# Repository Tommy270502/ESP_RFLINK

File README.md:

# Wireless Dev Bridge

Wireless Dev Bridge is a USB-C developer kit for ESP32-S3 and nRF24L01+ work. It gives one bench dongle a shared JSON command protocol over USB serial, HTTP, WebSocket, and BLE, plus a Python SDK, CLI, local web workbench, firmware browser dashboard, KiCad hardware source, and manufacturing outputs.

## Start Here

1. Read [Getting Started](docs/getting-started.md) for firmware build, SDK install, and first RF validation.
2. Use the local web workbench:

   ```bash
   pip install -r application/requirements.txt
   python application/main.py
   ```

3. Or install the SDK and CLI:

   ```bash
   cd sdk/python
   python -m pip install -e ".[all]"
   wdb discover
   wdb --serial COM5 identify
   wdb --serial COM5 diagnostics
   ```

4. For a two-dongle kit, flash one `node1` and one `node2`, then run:

   ```bash
   wdb pair-test --node1-serial COM5 --node2-serial COM6
   ```

## Product Surfaces

| Surface | Location | Description |
| --- | --- | --- |
| Firmware | `Firmware/ESP32_RFLINK` | PlatformIO ESP32-S3 firmware. |
| Local web workbench | `application` | FastAPI/browser host tool at `http://127.0.0.1:5173`. |
| SDK/CLI | `sdk/python` | Python SDK, CLI, examples, and hardware-free tests. |
| Firmware browser dashboard | `http://192.168.4.1` | Served by the dongle SoftAP. |
| Hardware | `hardware/kicad` | KiCad schematic and PCB source. |
| Manufacturing | `manufacturing/gerbers` | Current V1 Gerber/drill export. |

All transports share one command response envelope:

```json
{"ok":true,"cmd":"status","data":{},"error":null}
```

See [Project Overview](project-overview.md) for interfaces, validated bench workflows, and architecture detail.

## Protocol 1.1 Capabilities

- Shared command envelope over USB serial, HTTP, WebSocket, and BLE.
- Runtime RF config, address management, send/listen/flush, and bridge toggles.
- Settings persistence through NVS with `settings_get`, `settings_set`, `settings_save`, and `settings_reset`.
- Diagnostics and identify commands for support and physical device matching.
- Optional token auth for HTTP, WebSocket, and BLE command surfaces.
- Support report export from the CLI and local web workbench.

## Development Checks

```bash
cd Firmware/ESP32_RFLINK
pio run -e node1 -e node2

cd ../../sdk/python
python -m pytest

cd ../..
python -m py_compile application/main.py
python scripts/check_docs_links.py
```

## Documentation

- [Documentation Index](docs/documentation-index.md)
- [Project Overview](project-overview.md)
- [Getting Started](docs/getting-started.md)
- [First Run](docs/first-run.md)
- [API Reference](docs/api-reference.md)
- [Firmware Guide](docs/firmware.md)
- [Hardware Guide](docs/hardware.md)
- [Security Model](docs/security-model.md)
- [Troubleshooting](docs/troubleshooting.md)
- [Release Checklist](docs/release-checklist.md)
- [Local Web Workbench](application/desktop-workbench.md)
- [Python SDK](sdk/python/python-sdk-guide.md)

## V1 Boundaries

- nRF24 payloads are limited to 32 bytes.
- nRF24 address width is fixed at 5 bytes.
- RF configuration is runtime-only until saved with protocol 1.1 settings commands.
- HTTP, WebSocket, and BLE APIs are intended for trusted developer/lab networks.
- OTA, cloud connectivity, packet decoding, persistence, and mesh networking are out of scope for V1.

## License

Software is licensed under the MIT License; see [LICENSE](LICENSE). Hardware source and manufacturing outputs use the hardware license notice in [hardware/LICENSE.md](hardware/LICENSE.md).

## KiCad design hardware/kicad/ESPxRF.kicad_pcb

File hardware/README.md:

# Hardware

KiCad hardware source and project-local mechanical assets for Wireless Dev Bridge V1.

Open the KiCad project at:

```text
hardware/kicad/ESPxRF.kicad_pro
```

Manufacturing outputs are kept separately in:

```text
manufacturing/gerbers
```

See [Hardware Guide](../docs/hardware.md) for board assets, KiCad notes, manufacturing review steps, and firmware pin alignment.

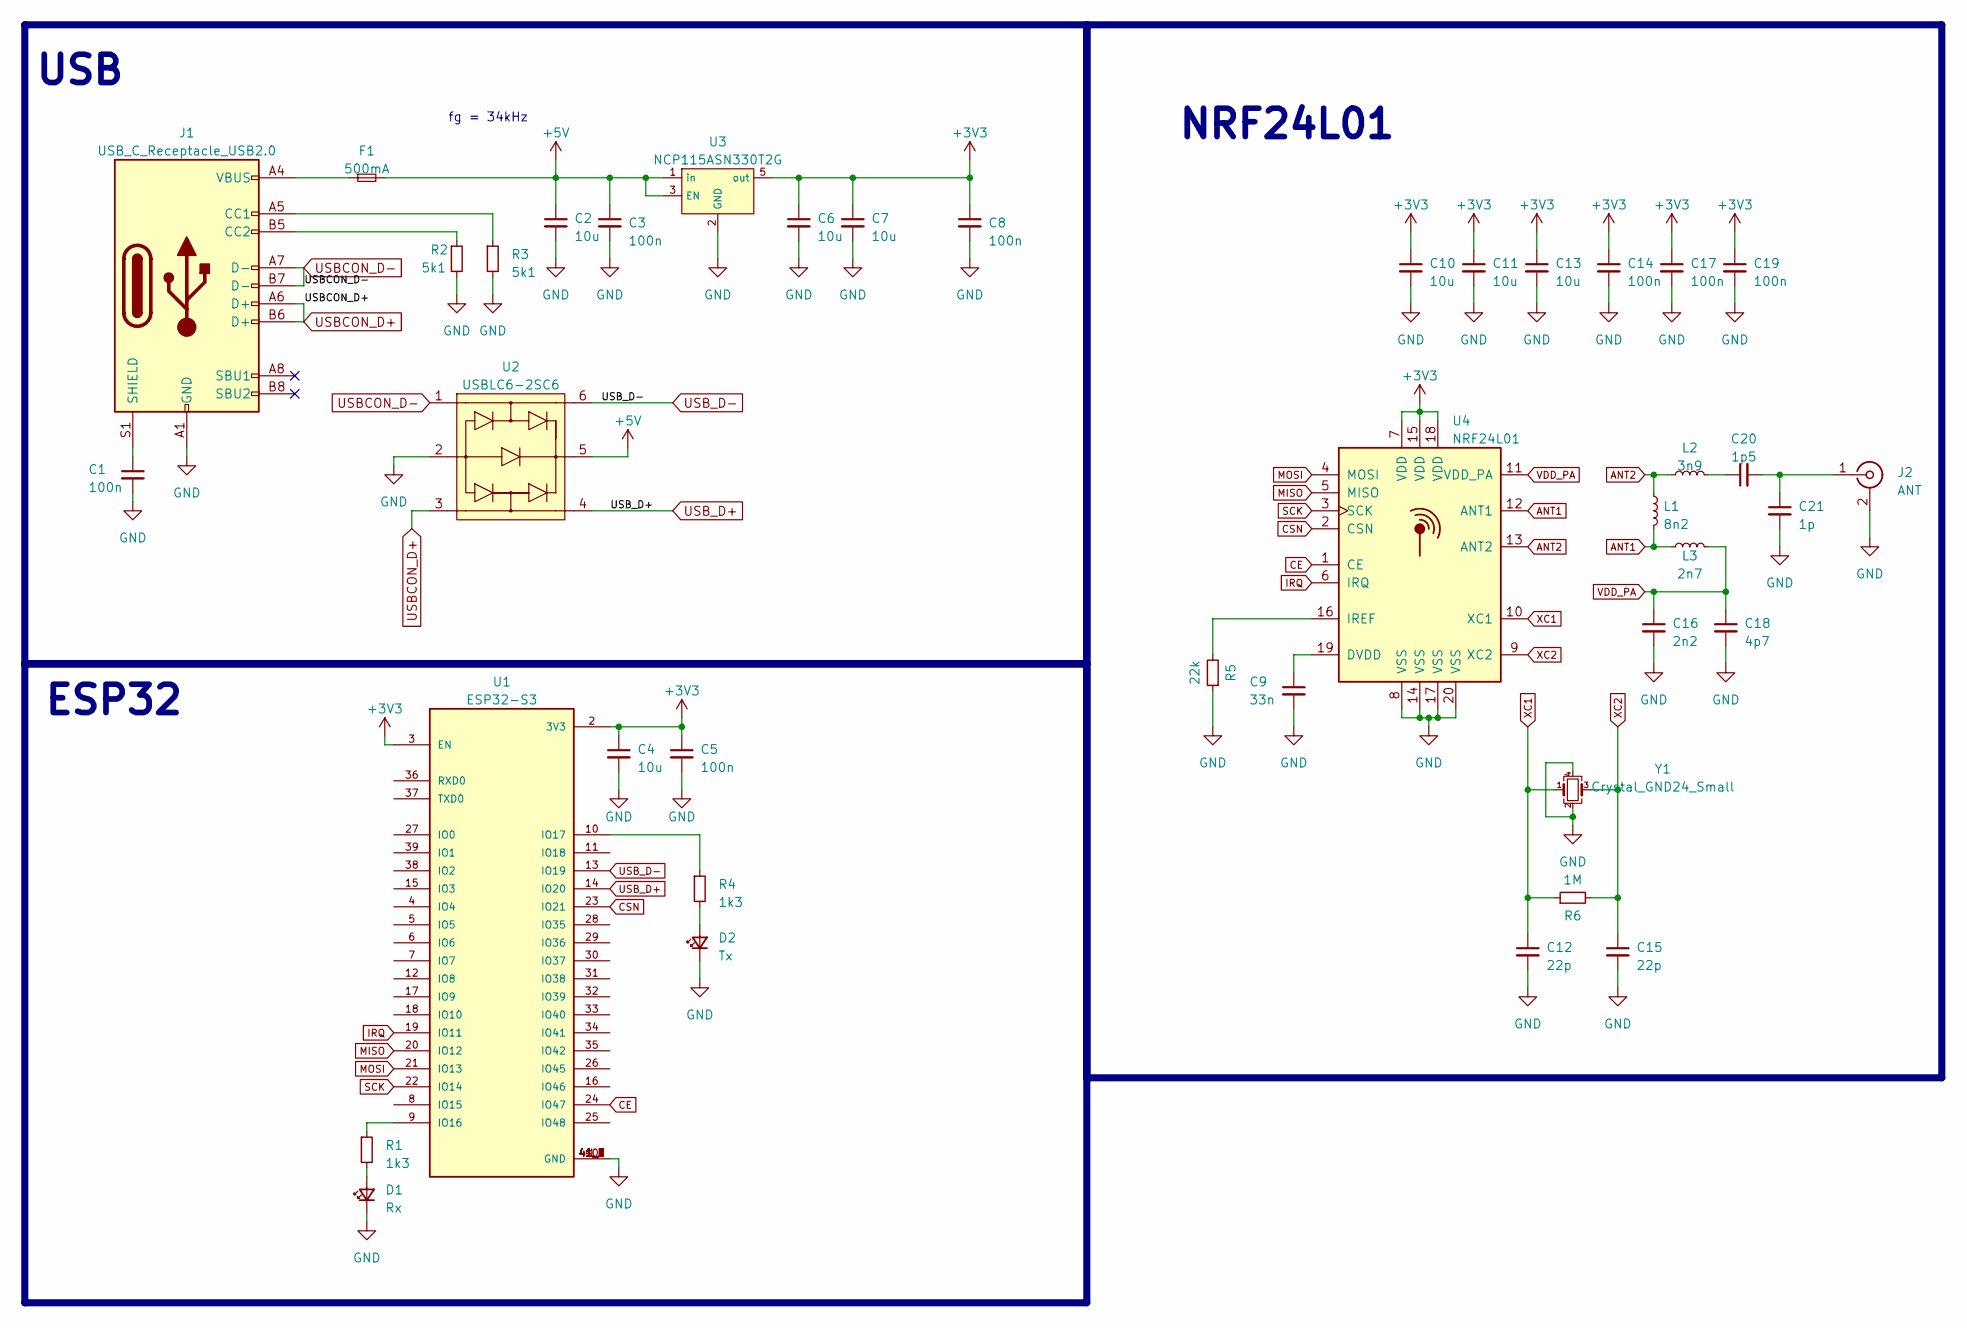
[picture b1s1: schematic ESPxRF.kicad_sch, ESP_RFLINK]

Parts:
C1, C3, C5, C8, C14, C17, C19: 100n; C_0603_1608Metric_Pad1.08x0.95mm_HandSolder
C2, C4, C6, C7, C10, C11, C13: 10u; C_0805_2012Metric_Pad1.18x1.45mm_HandSolder
C9: 33n; C_0603_1608Metric_Pad1.08x0.95mm_HandSolder
C12, C15: 22p; C_0603_1608Metric_Pad1.08x0.95mm_HandSolder
C16: 2n2; C_0402_1005Metric_Pad0.74x0.62mm_HandSolder
C18: 4p7; C_0402_1005Metric_Pad0.74x0.62mm_HandSolder
C20: 1p5; C_0402_1005Metric_Pad0.74x0.62mm_HandSolder
C21: 1p; C_0402_1005Metric_Pad0.74x0.62mm_HandSolder
D1: Rx; LED_0603_1608Metric_Pad1.05x0.95mm_HandSolder
D2: Tx; LED_0603_1608Metric_Pad1.05x0.95mm_HandSolder
F1: 500mA; Fuse_0603_1608Metric_Pad1.05x0.95mm_HandSolder
J1: USB_C_Receptacle_USB2.0; USB_C_Receptacle_GCT_USB4105-xx-A_16P_TopMnt_Horizontal
J2: ANT; SMA_Samtec_SMA-J-P-H-ST-EM1_EdgeMount
L1: 8n2; L_0402_1005Metric_Pad0.77x0.64mm_HandSolder
L2: 3n9; L_0402_1005Metric_Pad0.77x0.64mm_HandSolder
L3: 2n7; L_0402_1005Metric_Pad0.77x0.64mm_HandSolder
R1, R4: 1k3; R_0603_1608Metric_Pad0.98x0.95mm_HandSolder
R2, R3: 5k1; R_0603_1608Metric_Pad0.98x0.95mm_HandSolder
R5: 22k; R_0603_1608Metric_Pad0.98x0.95mm_HandSolder
R6: 1M; R_0603_1608Metric_Pad0.98x0.95mm_HandSolder
U1: ESP32-S3; XCVR_ESP32S3WROOM1N8R8
U2: USBLC6-2SC6; SOT-23-6_Handsoldering
U3: NCP115ASN330T2G; SOT-23-5_HandSoldering
U4: NRF24L01; QFN-20-1EP_4x4mm_P0.5mm_EP2.5x2.5mm
Y1: Crystal_GND24_Small; Crystal_SMD_2520-4Pin_2.5x2.0mm

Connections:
+3V3: C4.1, C5.1, C6.1, C7.1, C8.1, C10.1, C11.1, C13.1, C14.1, C17.1, C19.1, U1.2 (3V3), U1.3 (EN), U3.5 (out), U4.7 (VDD), U4.15 (VDD), U4.18 (VDD)
+5V: C2.1, C3.1, F1.2, U2.5, U3.1 (in), U3.3 (EN)
ANT1: L1.2, L3.1, U4.12 (ANT1)
ANT2: L1.1, L2.1, U4.13 (ANT2)
CE: U1.24 (IO47), U4.1 (CE)
CSN: U1.23 (IO21), U4.2 (CSN)
GND: C1.2, C2.2, C3.2, C4.2, C5.2, C6.2, C7.2, C8.2, C9.2, C10.2, C11.2, C12.2, C13.2, C14.2, C15.2, C16.2, C17.2, C18.2, C19.2, C21.2, D1.1 (K), D2.1 (K), J1.A1 (GND), J1.A12 (GND), J1.B1 (GND), J1.B12 (GND), J2.2 (Ext), R2.2, R3.2, R5.1, U1.1 (GND), U1.40 (GND), U1.41_1 (GND), U1.41_2 (GND), U1.41_3 (GND), U1.41_4 (GND), U1.41_5 (GND), U1.41_6 (GND), U1.41_7 (GND), U1.41_8 (GND), U1.41_9 (GND), U2.2, U3.2 (GND), U4.8 (VSS), U4.14 (VSS), U4.17 (VSS), U4.20 (VSS), Y1.2, Y1.4
IRQ: U1.19 (IO11), U4.6 (IRQ)
MISO: U1.20 (IO12), U4.5 (MISO)
MOSI: U1.21 (IO13), U4.4 (MOSI)
unnamed: C20.1, L2.2
unnamed: D1.2 (A), R1.2
unnamed: D2.2 (A), R4.2
unnamed: F1.1, J1.A4 (VBUS), J1.A9 (VBUS), J1.B4 (VBUS), J1.B9 (VBUS)
unnamed: J1.A5 (CC1), R3.1
unnamed: J1.B5 (CC2), R2.1
unnamed: C1.1, J1.S1 (SHIELD)
unnamed: C20.2, C21.1, J2.1 (In)
unnamed: R1.1, U1.9 (IO16)
unnamed: R4.1, U1.10 (IO17)
unnamed: C9.1, U4.19 (DVDD)
unnamed: R5.2, U4.16 (IREF)
SCK: U1.22 (IO14), U4.3 (SCK)
USBCON_D+: J1.A6 (D+), J1.B6 (D+), U2.3
USBCON_D-: J1.A7 (D-), J1.B7 (D-), U2.1
USB_D+: U1.14 (IO20), U2.4
USB_D-: U1.13 (IO19), U2.6
VDD_PA: C16.1, C18.1, L3.2, U4.11 (VDD_PA)
XC1: C12.1, R6.1, U4.10 (XC1), Y1.1
XC2: C15.1, R6.2, U4.9 (XC2), Y1.3

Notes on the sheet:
ESP32
fg = 34kHz
USB
NRF24L01

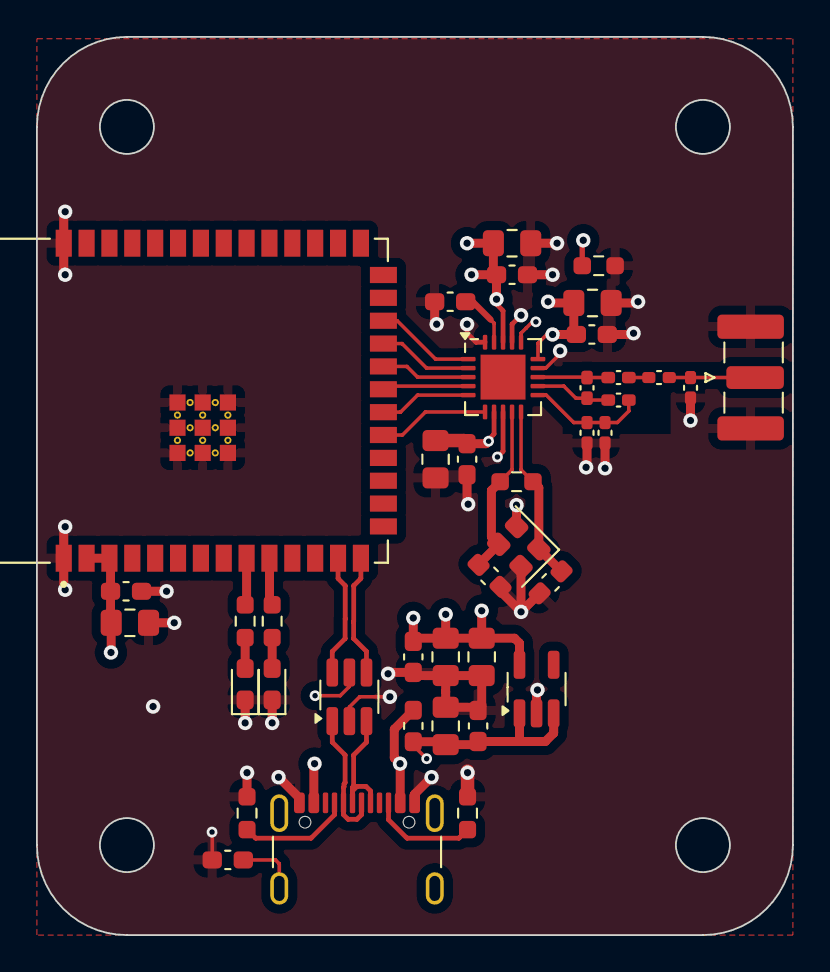
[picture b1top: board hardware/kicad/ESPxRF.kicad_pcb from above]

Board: 4 copper layers, 42.0 x 49.9 mm, 40 parts (0 on the bottom side), 30 nets.

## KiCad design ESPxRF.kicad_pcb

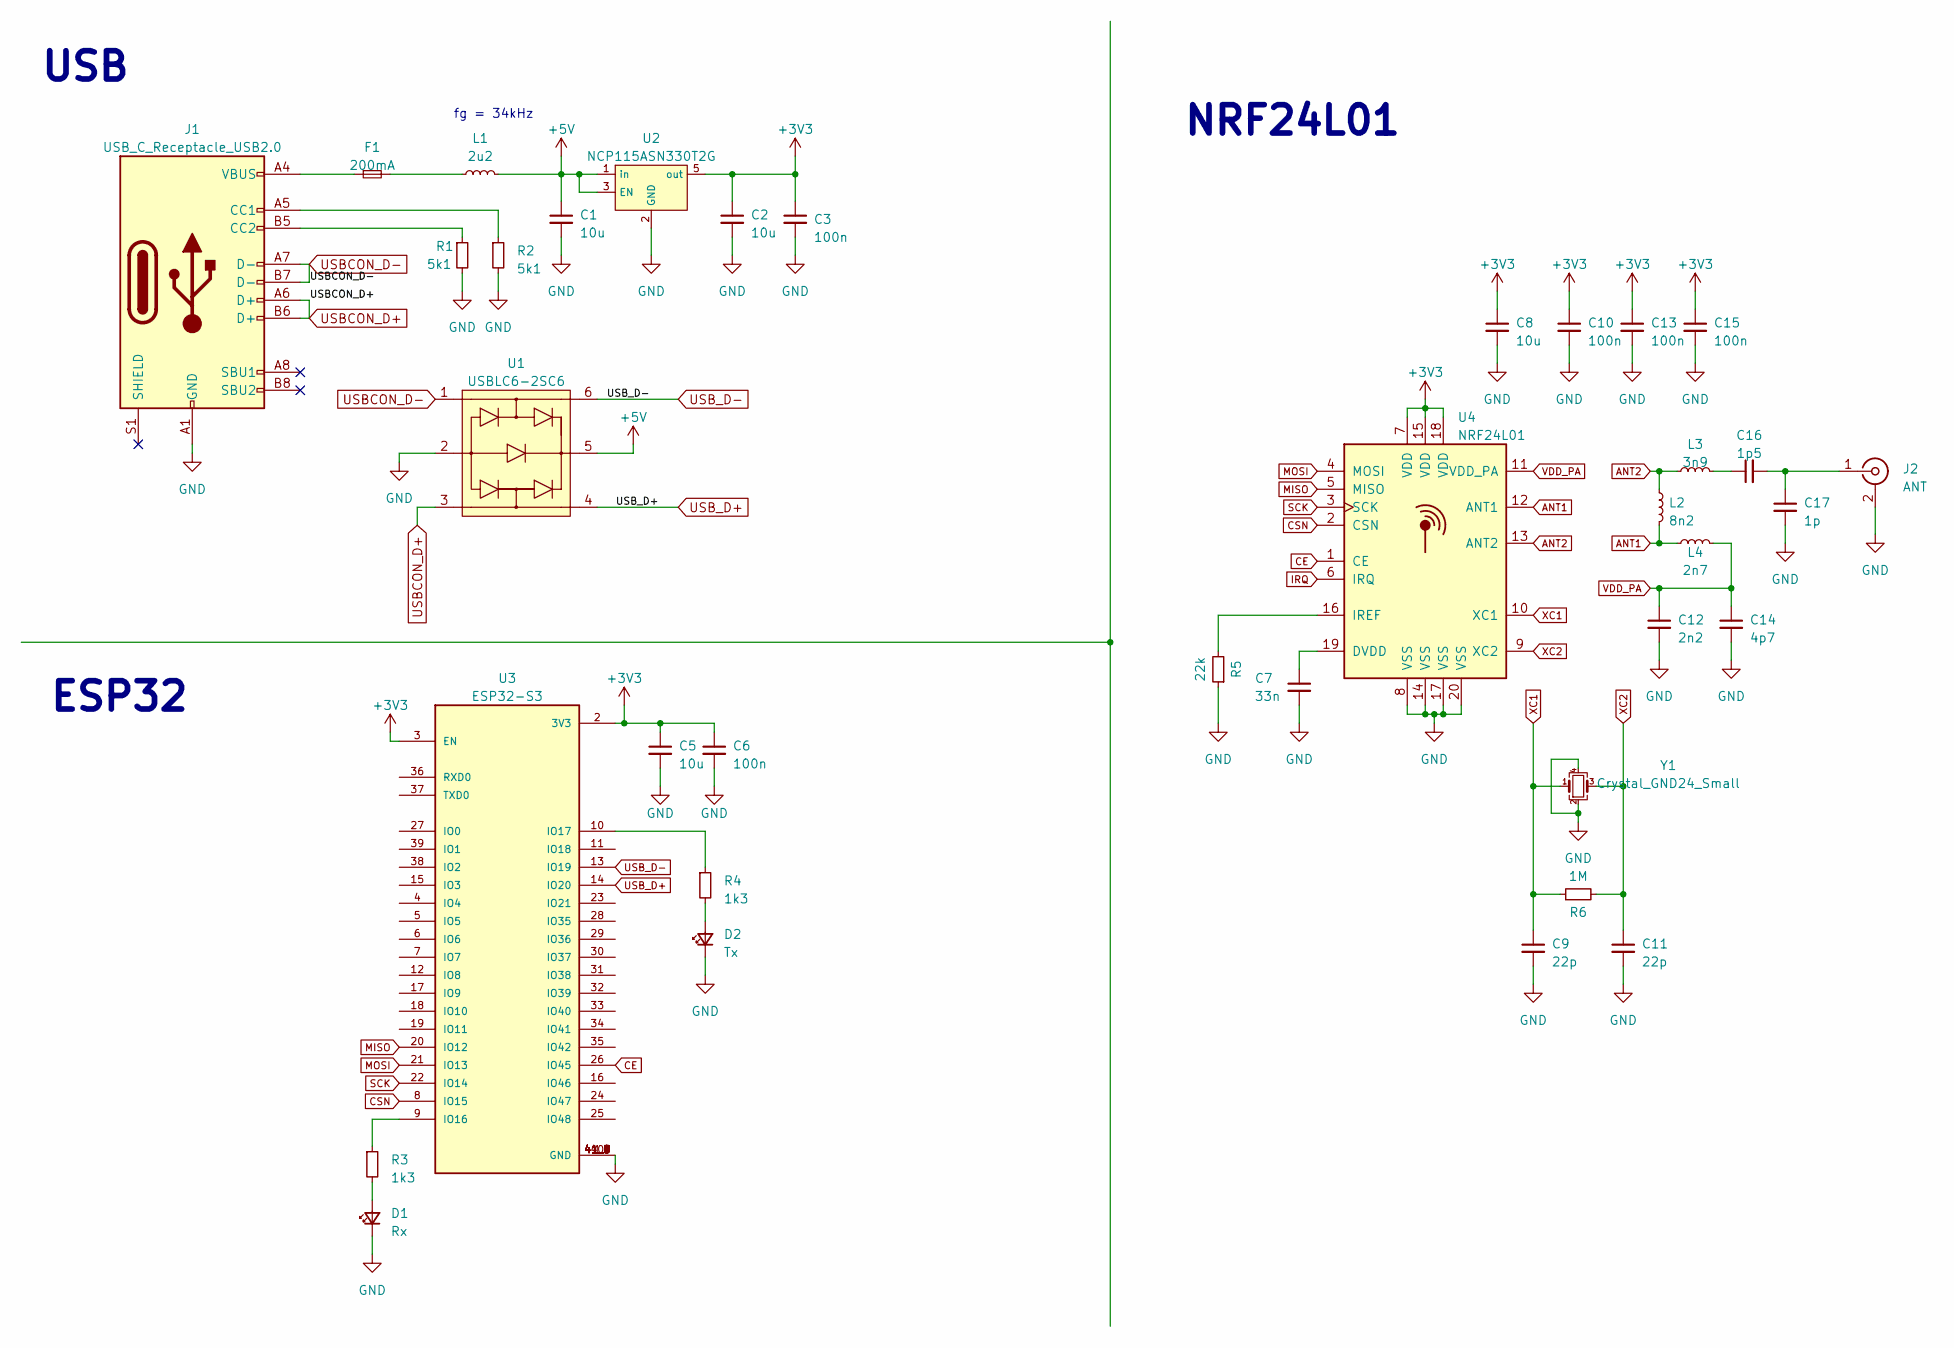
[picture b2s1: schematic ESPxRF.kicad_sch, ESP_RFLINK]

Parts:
C1, C2, C5, C8: 10u; C_0603_1608Metric_Pad1.08x0.95mm_HandSolder
C3, C6: 100n; C_0603_1608Metric_Pad1.08x0.95mm_HandSolder
C7: 33n; C_0402_1005Metric_Pad0.74x0.62mm_HandSolder
C9, C11: 22p; C_0402_1005Metric_Pad0.74x0.62mm_HandSolder
C10, C13, C15: 100n; C_0402_1005Metric_Pad0.74x0.62mm_HandSolder
C12: 2n2; C_0402_1005Metric_Pad0.74x0.62mm_HandSolder
C14: 4p7; C_0402_1005Metric_Pad0.74x0.62mm_HandSolder
C16: 1p5; C_0402_1005Metric_Pad0.74x0.62mm_HandSolder
C17: 1p; C_0402_1005Metric_Pad0.74x0.62mm_HandSolder
D1: Rx; LED_0603_1608Metric_Pad1.05x0.95mm_HandSolder
D2: Tx; LED_0603_1608Metric_Pad1.05x0.95mm_HandSolder
F1: 200mA; Fuse_0603_1608Metric_Pad1.05x0.95mm_HandSolder
J1: USB_C_Receptacle_USB2.0; USB_C_Receptacle_GCT_USB4105-xx-A_16P_TopMnt_Horizontal
J2: ANT; SMA_Samtec_SMA-J-P-X-ST-EM1_EdgeMount
L1: 2u2; L_0603_1608Metric_Pad1.05x0.95mm_HandSolder
L2: 8n2; L_0402_1005Metric_Pad0.77x0.64mm_HandSolder
L3: 3n9; L_0402_1005Metric_Pad0.77x0.64mm_HandSolder
L4: 2n7; L_0402_1005Metric_Pad0.77x0.64mm_HandSolder
R1, R2: 5k1; R_0603_1608Metric_Pad0.98x0.95mm_HandSolder
R3, R4: 1k3; R_0603_1608Metric_Pad0.98x0.95mm_HandSolder
R5: 22k; R_0402_1005Metric_Pad0.72x0.64mm_HandSolder
R6: 1M; R_0402_1005Metric_Pad0.72x0.64mm_HandSolder
U1: USBLC6-2SC6; SOT-23-6_Handsoldering
U2: NCP115ASN330T2G; SOT-23-5_HandSoldering
U3: ESP32-S3; XCVR_ESP32S3WROOM1N8R8
U4: NRF24L01; QFN-20-1EP_4x4mm_P0.5mm_EP2.5x2.5mm
Y1: Crystal_GND24_Small; Crystal_SMD_2520-4Pin_2.5x2.0mm

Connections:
+3V3: C2.1, C3.1, C5.1, C6.1, C8.1, C10.1, C13.1, C15.1, U2.5 (out), U3.2 (3V3), U3.3 (EN), U4.7 (VDD), U4.15 (VDD), U4.18 (VDD)
+5V: C1.1, L1.2, U1.5, U2.1 (in), U2.3 (EN)
ANT1: L2.2, L4.1, U4.12 (ANT1)
ANT2: L2.1, L3.1, U4.13 (ANT2)
CE: U3.26 (IO45), U4.1 (CE)
CSN: U3.8 (IO15), U4.2 (CSN)
GND: C1.2, C2.2, C3.2, C5.2, C6.2, C7.2, C8.2, C9.2, C10.2, C11.2, C12.2, C13.2, C14.2, C15.2, C17.2, D1.1 (K), D2.1 (K), J1.A1 (GND), J1.A12 (GND), J1.B1 (GND), J1.B12 (GND), J2.2 (Ext), R1.2, R2.2, R5.1, U1.2, U2.2 (GND), U3.1 (GND), U3.40 (GND), U3.41_1 (GND), U3.41_2 (GND), U3.41_3 (GND), U3.41_4 (GND), U3.41_5 (GND), U3.41_6 (GND), U3.41_7 (GND), U3.41_8 (GND), U3.41_9 (GND), U4.8 (VSS), U4.14 (VSS), U4.17 (VSS), U4.20 (VSS), Y1.2, Y1.4
IRQ: U4.6 (IRQ)
MISO: U3.20 (IO12), U4.5 (MISO)
MOSI: U3.21 (IO13), U4.4 (MOSI)
unnamed: C16.1, L3.2
unnamed: D1.2 (A), R3.2
unnamed: D2.2 (A), R4.2
unnamed: F1.1, J1.A4 (VBUS), J1.A9 (VBUS), J1.B4 (VBUS), J1.B9 (VBUS)
unnamed: F1.2, L1.1
unnamed: J1.A5 (CC1), R2.1
unnamed: J1.B5 (CC2), R1.1
unnamed: C16.2, C17.1, J2.1 (In)
unnamed: R3.1, U3.9 (IO16)
unnamed: R4.1, U3.10 (IO17)
unnamed: C7.1, U4.19 (DVDD)
unnamed: R5.2, U4.16 (IREF)
SCK: U3.22 (IO14), U4.3 (SCK)
USBCON_D+: J1.A6 (D+), J1.B6 (D+), U1.3
USBCON_D-: J1.A7 (D-), J1.B7 (D-), U1.1
USB_D+: U1.4, U3.14 (IO20)
USB_D-: U1.6, U3.13 (IO19)
VDD_PA: C12.1, C14.1, L4.2, U4.11 (VDD_PA)
XC1: C9.1, R6.1, U4.10 (XC1), Y1.1
XC2: C11.1, R6.2, U4.9 (XC2), Y1.3

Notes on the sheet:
ESP32
fg = 34kHz
USB
NRF24L01

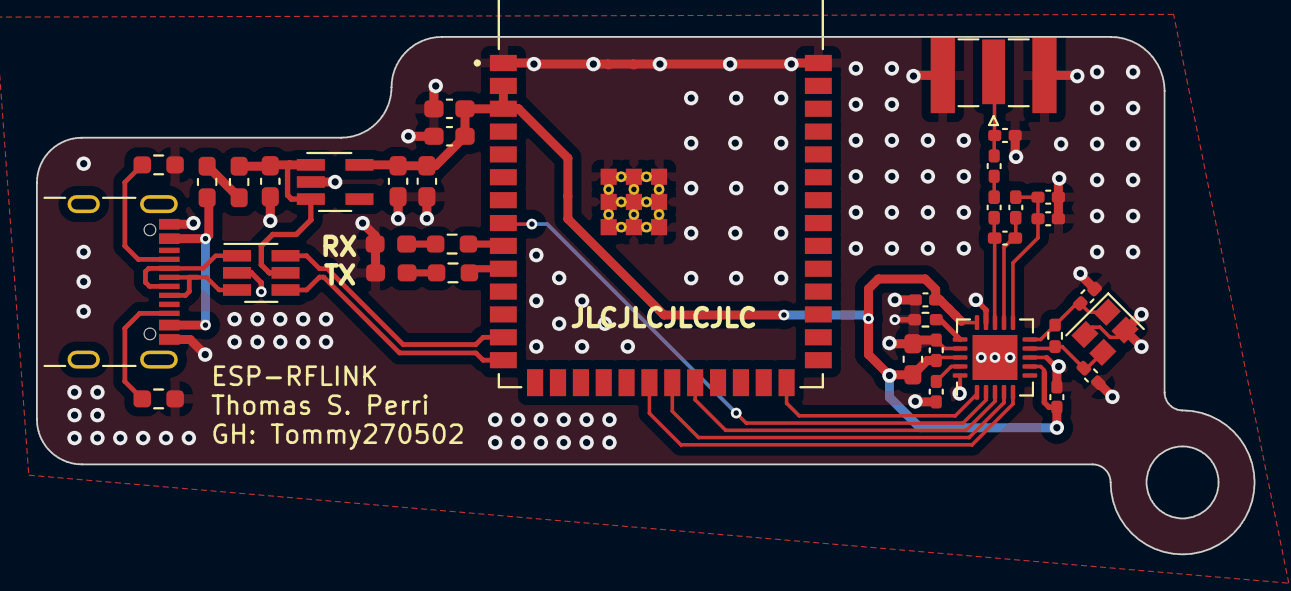
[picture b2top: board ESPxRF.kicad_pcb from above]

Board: 4 copper layers, 67.6 x 28.7 mm, 36 parts (0 on the bottom side), 29 nets.

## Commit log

2023-08-25 finished nrf schematic
2023-08-25 nearly finished V1
2023-08-25 ground pour and optimizations
2023-08-25 added side mouting hole for I guess keyrings
2023-08-25 made the ring sturdier and m2
2023-08-25 added pcb size measurements
2023-08-29 testing on second pc
2023-08-29 added GND plane in two inner layers
2023-08-29 added silkscreen name
2023-08-29 went through the DRC and assigned my own kicad libraries
2023-08-31 added jlc silkscreen tidied schematic
2023-09-30 fixed short usb esd protection IC
2023-09-30 fixed usb differential pair
2023-10-02 fixed order number jlc
2023-10-02 added 3d models
2023-10-03 generated gerber
2023-10-05 cleanup
2023-10-10 removed 0.4mm/0.2mm via from esp32 footprint
2026-05-04 added firmware
2026-05-04 added sdk
2026-05-04 tested sdk
2026-05-04 improved test examples
2026-05-04 added bt
2026-05-05 implement rf_to_ble
2026-05-05 Organize V1 developer launch package
2026-05-05 Add two-dongle production demo
2026-05-06 Rev.2 PCB improved layout
2026-05-06 added keepout area for antenna and impedance matching network
2026-05-15 Integrate desktop workbench and refresh docs
2026-05-21 renamed all markdown files
2026-05-21 Productize Wireless Dev Bridge developer kit
2026-05-24 made webapp
2026-05-26 Implement repository cleanup roadmap
